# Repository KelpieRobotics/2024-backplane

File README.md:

# 2024-MainBoard
schematics and PCB designs for 2024 MainBoard go here

## how to use

### symbol library
in KiCAD, symbol editor > preferences > manage symbol libraries
press the folder icon and select the file in libs/symbols/

### footprint library
same steps but select the folder in libs/footprints

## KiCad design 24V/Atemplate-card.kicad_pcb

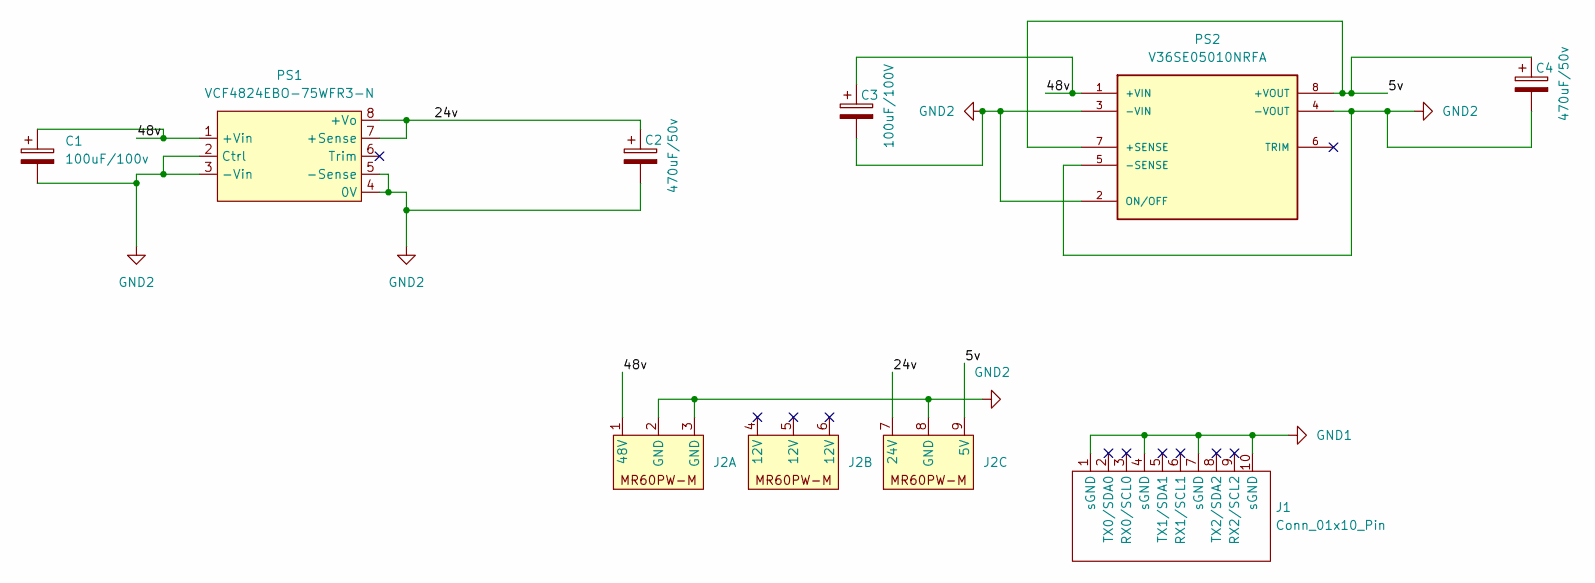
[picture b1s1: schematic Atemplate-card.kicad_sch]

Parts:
C1: 100uF/100v; CP_Elec_10x12.5
C2, C4: 470uF/50v; CP_Elec_10x12.5
C3: 100uF/100V; CP_Elec_10x12.5
J1: Conn_01x10_Pin; CardEdge_2x10
J2: MR60PW-M_X3
PS1: VCF4824EBO-75WFR3-N; Mornsun VCF4824EBO-75WFR3-N
PS2: V36SE05010NRFA; Delta V36SE05010NRFA; PARTREV 03282018

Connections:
/5v: C4.1, J2.9 (5V), PS2.7 (+SENSE), PS2.8 (+VOUT)
/24v: C2.1, J2.7 (24V), PS1.7 (+Sense), PS1.8 (+Vo)
/48v: C1.1, C3.1, J2.1 (48V), PS1.1 (+Vin), PS2.1 (+VIN)
GND1: J1.1 (sGND), J1.4 (sGND), J1.7 (sGND), J1.10 (sGND)
GND2: C1.2, C2.2, C3.2, C4.2, J2.2 (GND), J2.3 (GND), J2.8 (GND), PS1.2 (Ctrl), PS1.3 (-Vin), PS1.4 (0V), PS1.5 (-Sense), PS2.2 (ON/OFF), PS2.3 (-VIN), PS2.4 (-VOUT), PS2.5 (-SENSE)

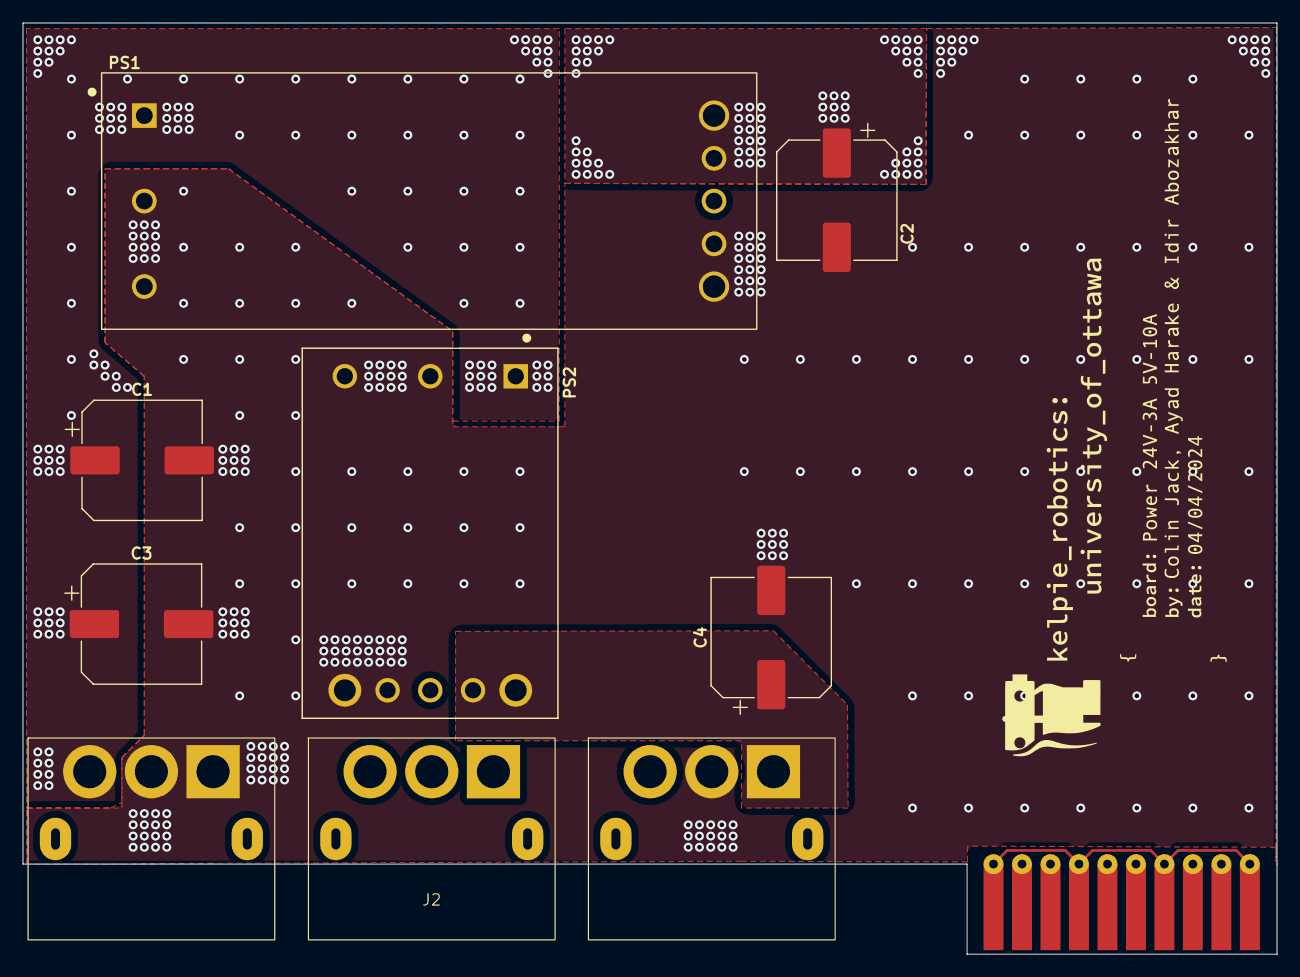
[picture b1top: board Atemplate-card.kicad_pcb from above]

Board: 2 copper layers, 111.8 x 83.0 mm, 8 parts (0 on the bottom side), 5 nets.

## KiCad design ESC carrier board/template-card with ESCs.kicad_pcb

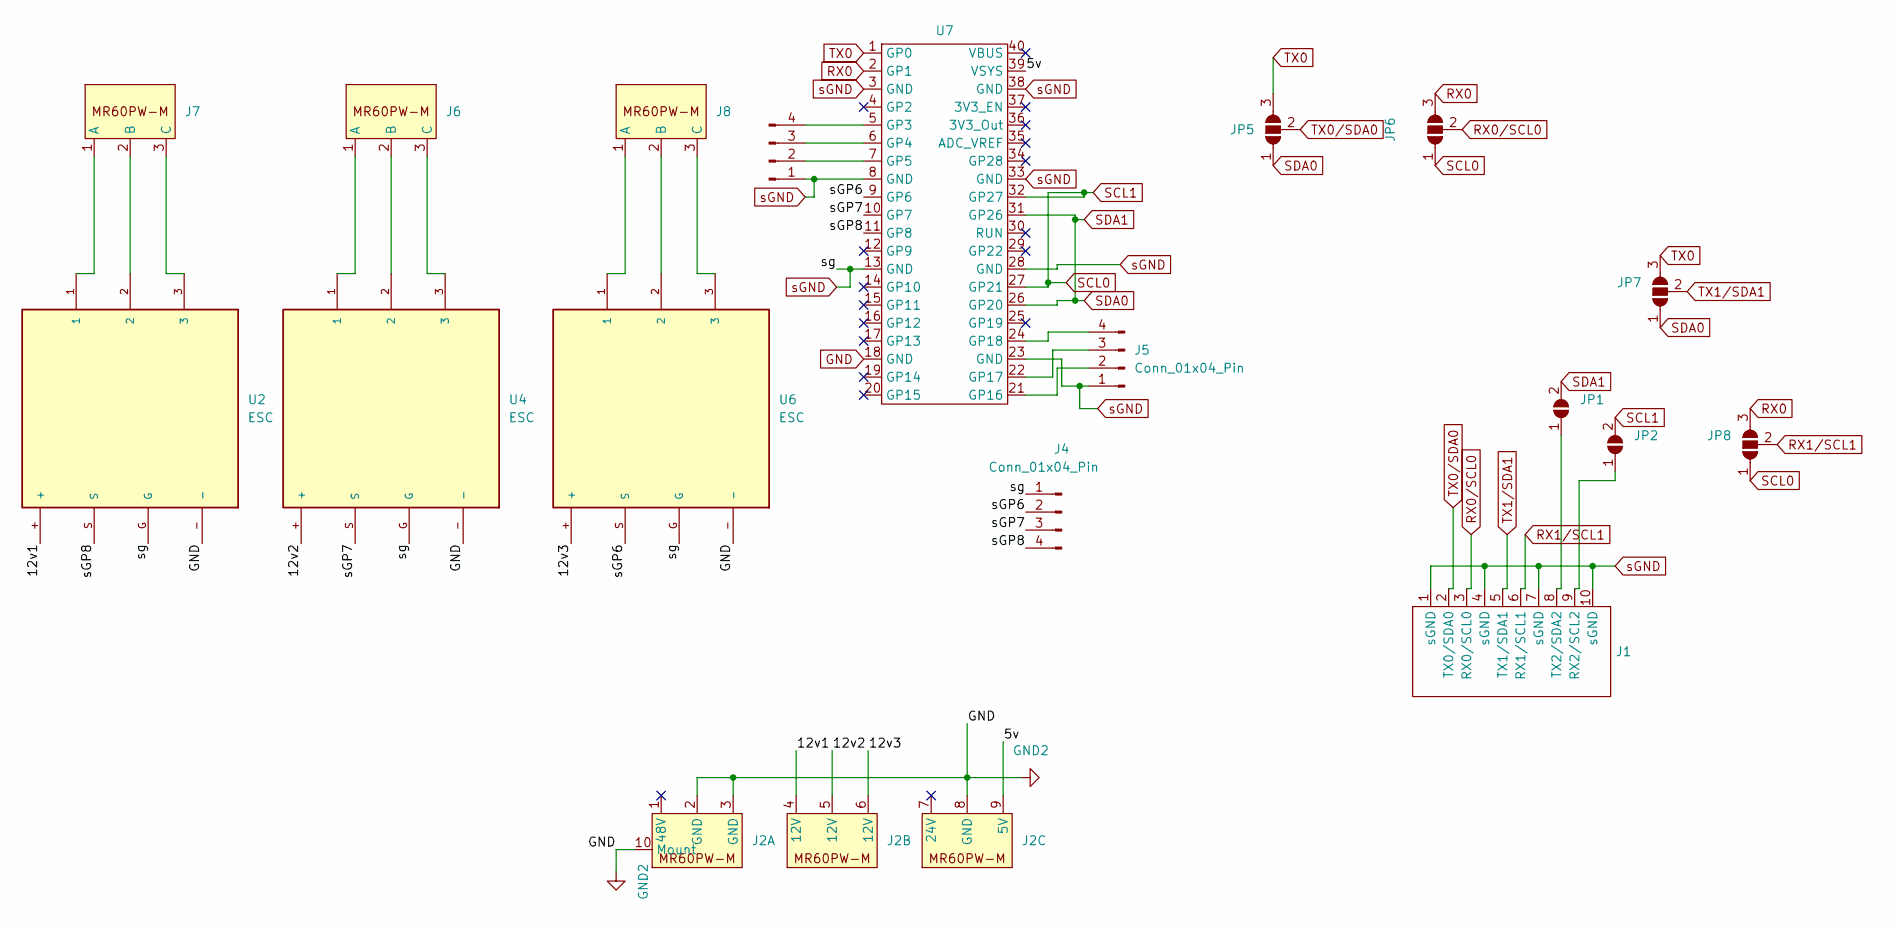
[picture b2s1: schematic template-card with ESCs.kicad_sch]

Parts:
J1: CardEdge_2x10
J2: MR60PW-M_X3
J3, J4, J5: Conn_01x04_Pin; PinHeader_1x04_P2.54mm_Horizontal
J6, J7, J8: MR60PW-M
JP1, JP2: SolderJumper_2_Open; SolderJumper-2_P1.3mm_Open_Pad1.0x1.5mm
JP5, JP6, JP7, JP8: SolderJumper_3_Open; SolderJumper-3_P2.0mm_Open_TrianglePad1.0x1.5mm
U2, U4, U6: ESC
U7: ESP32-S3-Pico

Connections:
/5v: J2.9 (5V), U7.39 (VSYS)
/12v1: J2.4 (12V), U2.+
/12v2: J2.5 (12V), U4.+
/12v3: J2.6 (12V), U6.+
/sGP6: J4.2, U6.S, U7.9 (GP6)
/sGP7: J4.3, U4.S, U7.10 (GP7)
/sGP8: J4.4, U2.S, U7.11 (GP8)
GND: J2.2 (GND), J2.3 (GND), J2.8 (GND), J2.10 (Mount), U2.-, U4.-, U6.-, U7.18 (GND)
unnamed: J1.9 (RX2/SCL2), JP2.1 (A)
unnamed: J1.8 (TX2/SDA2), JP1.1 (A)
unnamed: J3.2, U7.7 (GP5)
unnamed: J3.3, U7.6 (GP4)
unnamed: J3.4, U7.5 (GP3)
unnamed: J5.2, U7.21 (GP16)
unnamed: J5.3, U7.22 (GP17)
unnamed: J5.4, U7.24 (GP18)
unnamed: J6.1 (A), U4.1
unnamed: J6.2 (B), U4.2
unnamed: J6.3 (C), U4.3
unnamed: J7.1 (A), U2.1
unnamed: J7.2 (B), U2.2
unnamed: J7.3 (C), U2.3
unnamed: J8.1 (A), U6.1
unnamed: J8.2 (B), U6.2
unnamed: J8.3 (C), U6.3
RX0: JP6.3 (B), JP8.3 (B), U7.2 (GP1)
RX0/SCL0: J1.3 (RX0/SCL0), JP6.2 (C)
RX1/SCL1: J1.6 (RX1/SCL1), JP8.2 (C)
SCL0: JP2.2 (B), JP6.1 (A), JP8.1 (A), U7.27 (GP21), U7.32 (GP27)
SDA0: JP1.2 (B), JP5.1 (A), JP7.1 (A), U7.26 (GP20), U7.31 (GP26)
TX0: JP5.3 (B), JP7.3 (B), U7.1 (GP0)
TX0/SDA0: J1.2 (TX0/SDA0), JP5.2 (C)
TX1/SDA1: J1.5 (TX1/SDA1), JP7.2 (C)
sGND: J1.1 (sGND), J1.4 (sGND), J1.7 (sGND), J1.10 (sGND), J3.1, J4.1, J5.1, U2.G, U4.G, U6.G, U7.3 (GND), U7.8 (GND), U7.13 (GND), U7.23 (GND), U7.28 (GND), U7.33 (GND), U7.38 (GND)

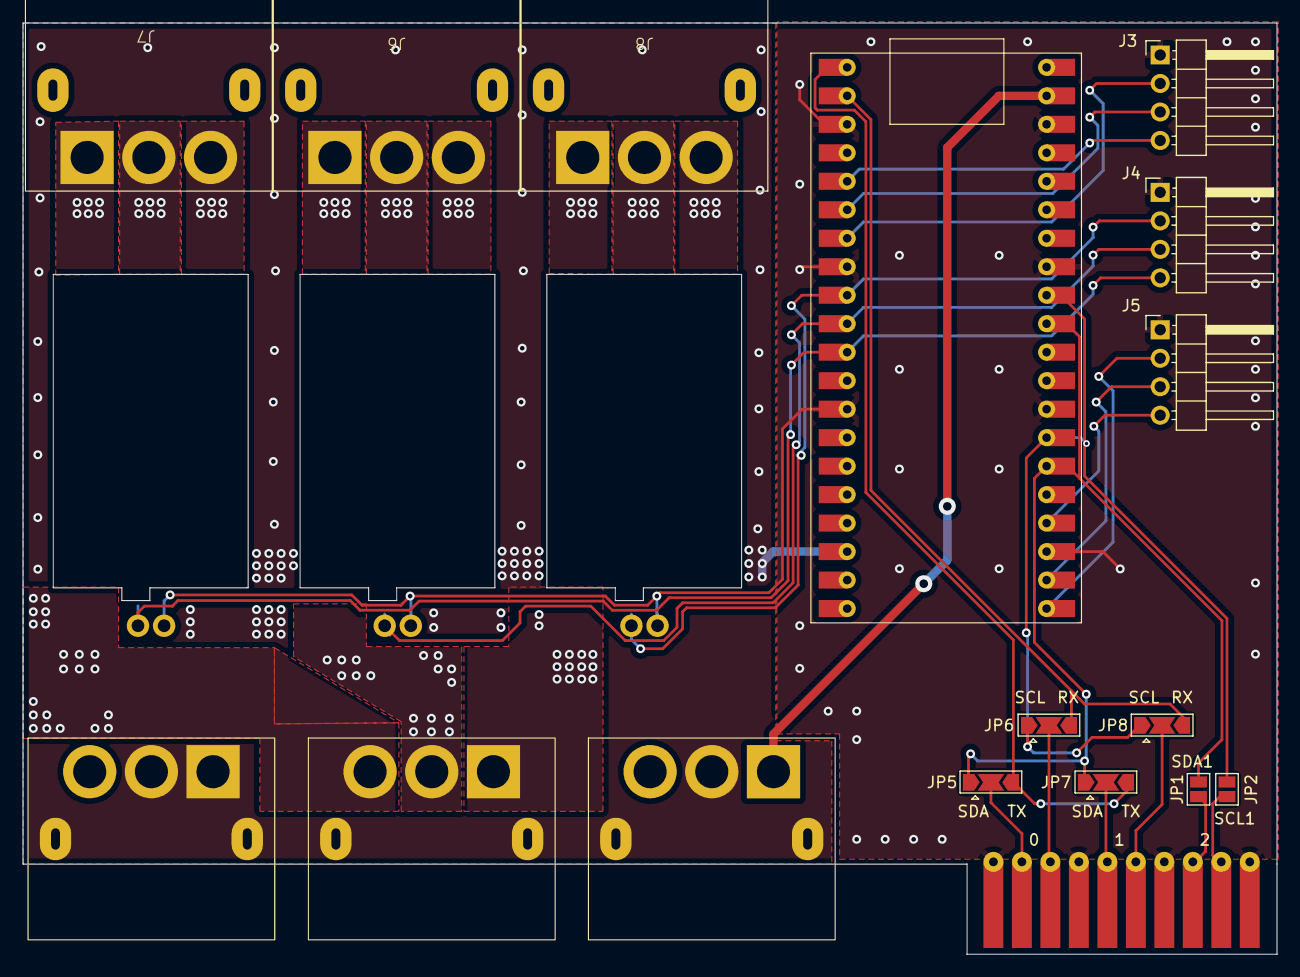
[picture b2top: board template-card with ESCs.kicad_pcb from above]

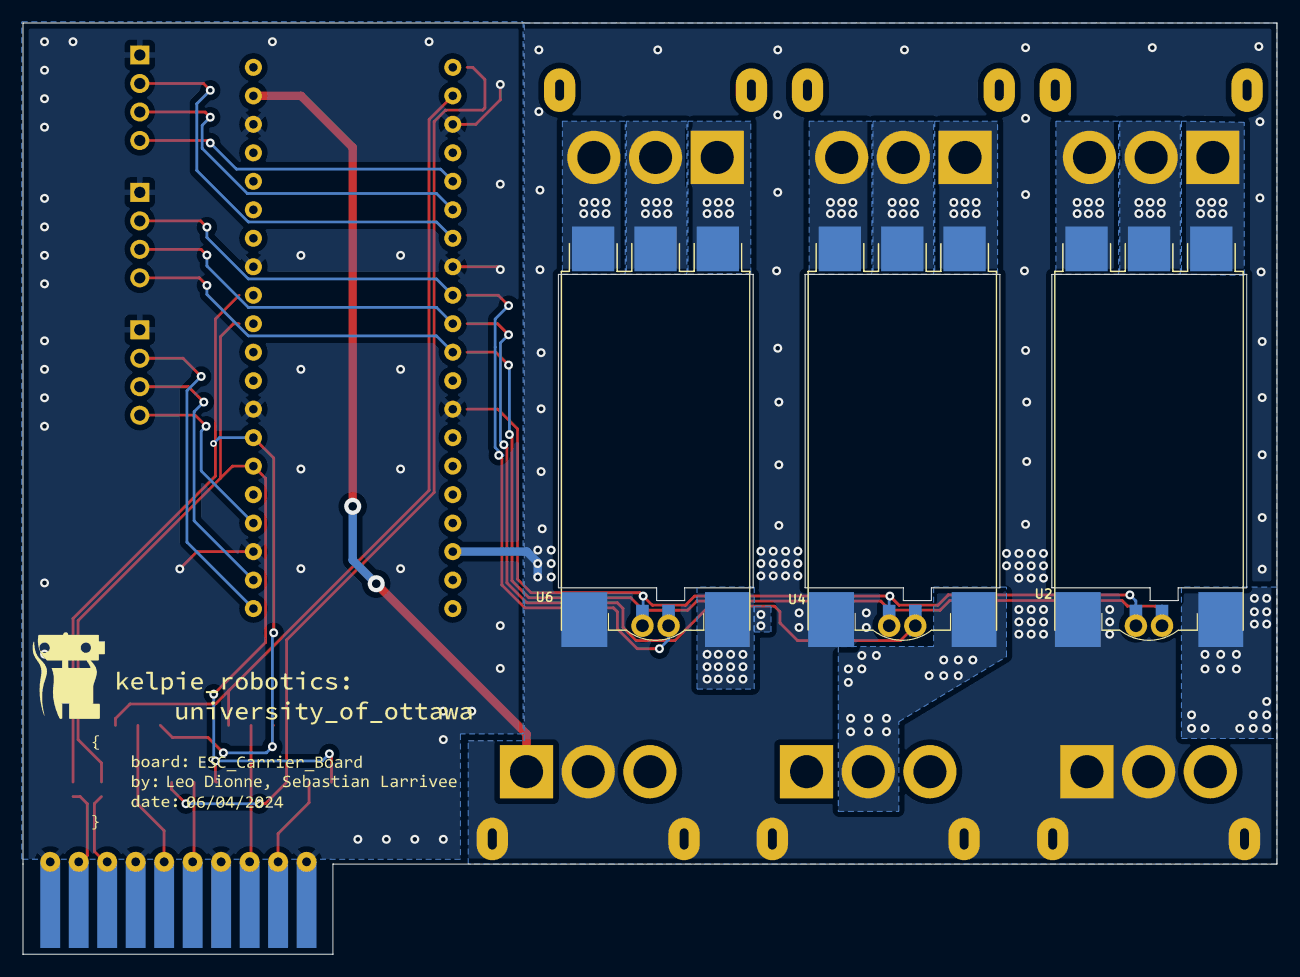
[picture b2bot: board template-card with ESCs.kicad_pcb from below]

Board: 2 copper layers, 111.8 x 83.0 mm, 18 parts (3 on the bottom side), 34 nets.

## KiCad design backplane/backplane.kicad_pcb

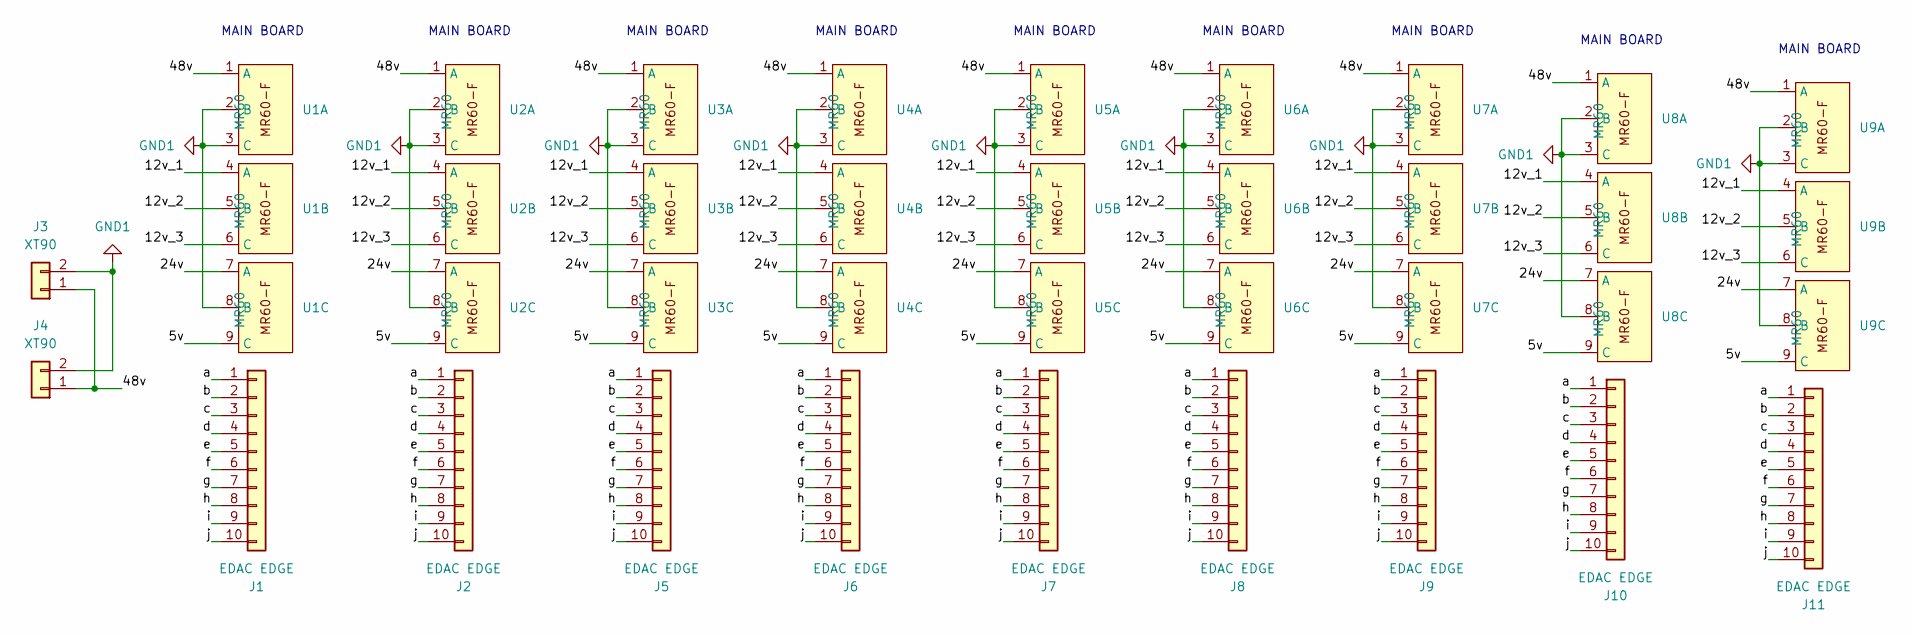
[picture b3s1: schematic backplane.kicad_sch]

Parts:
J1, J2, J5, J6, J7, J8, J9, J10, J11: EDAC EDGE; EDAC_Edge_2x10
J3, J4: XT90; AMASS_XT90PW-M_MOD_NUMS
U1, U2, U3, U4, U5, U6, U7, U8, U9: MR60; MR60-F_X3

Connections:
/5v: U1.9 (C), U2.9 (C), U3.9 (C), U4.9 (C), U5.9 (C), U6.9 (C), U7.9 (C), U8.9 (C), U9.9 (C)
/12v_1: U1.4 (A), U2.4 (A), U3.4 (A), U4.4 (A), U5.4 (A), U6.4 (A), U7.4 (A), U8.4 (A), U9.4 (A)
/12v_2: U1.5 (B), U2.5 (B), U3.5 (B), U4.5 (B), U5.5 (B), U6.5 (B), U7.5 (B), U8.5 (B), U9.5 (B)
/12v_3: U1.6 (C), U2.6 (C), U3.6 (C), U4.6 (C), U5.6 (C), U6.6 (C), U7.6 (C), U8.6 (C), U9.6 (C)
/24v: U1.7 (A), U2.7 (A), U3.7 (A), U4.7 (A), U5.7 (A), U6.7 (A), U7.7 (A), U8.7 (A), U9.7 (A)
/48v: J3.1, J4.1, U1.1 (A), U2.1 (A), U3.1 (A), U4.1 (A), U5.1 (A), U6.1 (A), U7.1 (A), U8.1 (A), U9.1 (A)
/a: J1.1, J2.1, J5.1, J6.1, J7.1, J8.1, J9.1, J10.1, J11.1
/b: J1.2, J2.2, J5.2, J6.2, J7.2, J8.2, J9.2, J10.2, J11.2
/c: J1.3, J2.3, J5.3, J6.3, J7.3, J8.3, J9.3, J10.3, J11.3
/d: J1.4, J2.4, J5.4, J6.4, J7.4, J8.4, J9.4, J10.4, J11.4
/e: J1.5, J2.5, J5.5, J6.5, J7.5, J8.5, J9.5, J10.5, J11.5
/f: J1.6, J2.6, J5.6, J6.6, J7.6, J8.6, J9.6, J10.6, J11.6
/g: J1.7, J2.7, J5.7, J6.7, J7.7, J8.7, J9.7, J10.7, J11.7
/h: J1.8, J2.8, J5.8, J6.8, J7.8, J8.8, J9.8, J10.8, J11.8
/i: J1.9, J2.9, J5.9, J6.9, J7.9, J8.9, J9.9, J10.9, J11.9
/j: J1.10, J2.10, J5.10, J6.10, J7.10, J8.10, J9.10, J10.10, J11.10
GND1: J3.2, J4.2, U1.2 (B), U1.3 (C), U1.8 (B), U2.2 (B), U2.3 (C), U2.8 (B), U3.2 (B), U3.3 (C), U3.8 (B), U4.2 (B), U4.3 (C), U4.8 (B), U5.2 (B), U5.3 (C), U5.8 (B), U6.2 (B), U6.3 (C), U6.8 (B), U7.2 (B), U7.3 (C), U7.8 (B), U8.2 (B), U8.3 (C), U8.8 (B), U9.2 (B), U9.3 (C), U9.8 (B)

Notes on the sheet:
MAIN BOARD

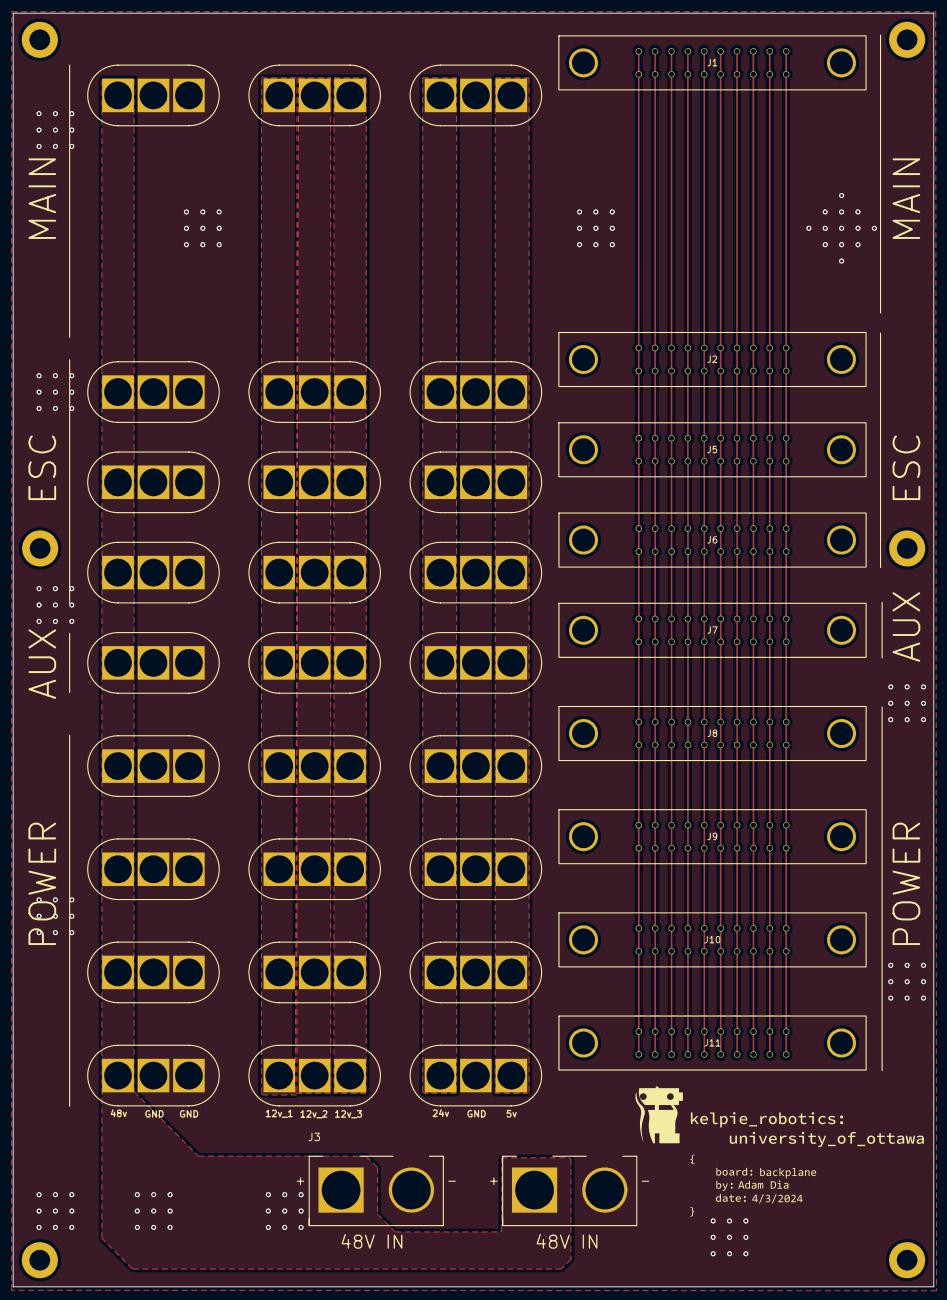
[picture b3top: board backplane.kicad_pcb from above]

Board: 2 copper layers, 142.8 x 197.5 mm, 20 parts (0 on the bottom side), 17 nets.

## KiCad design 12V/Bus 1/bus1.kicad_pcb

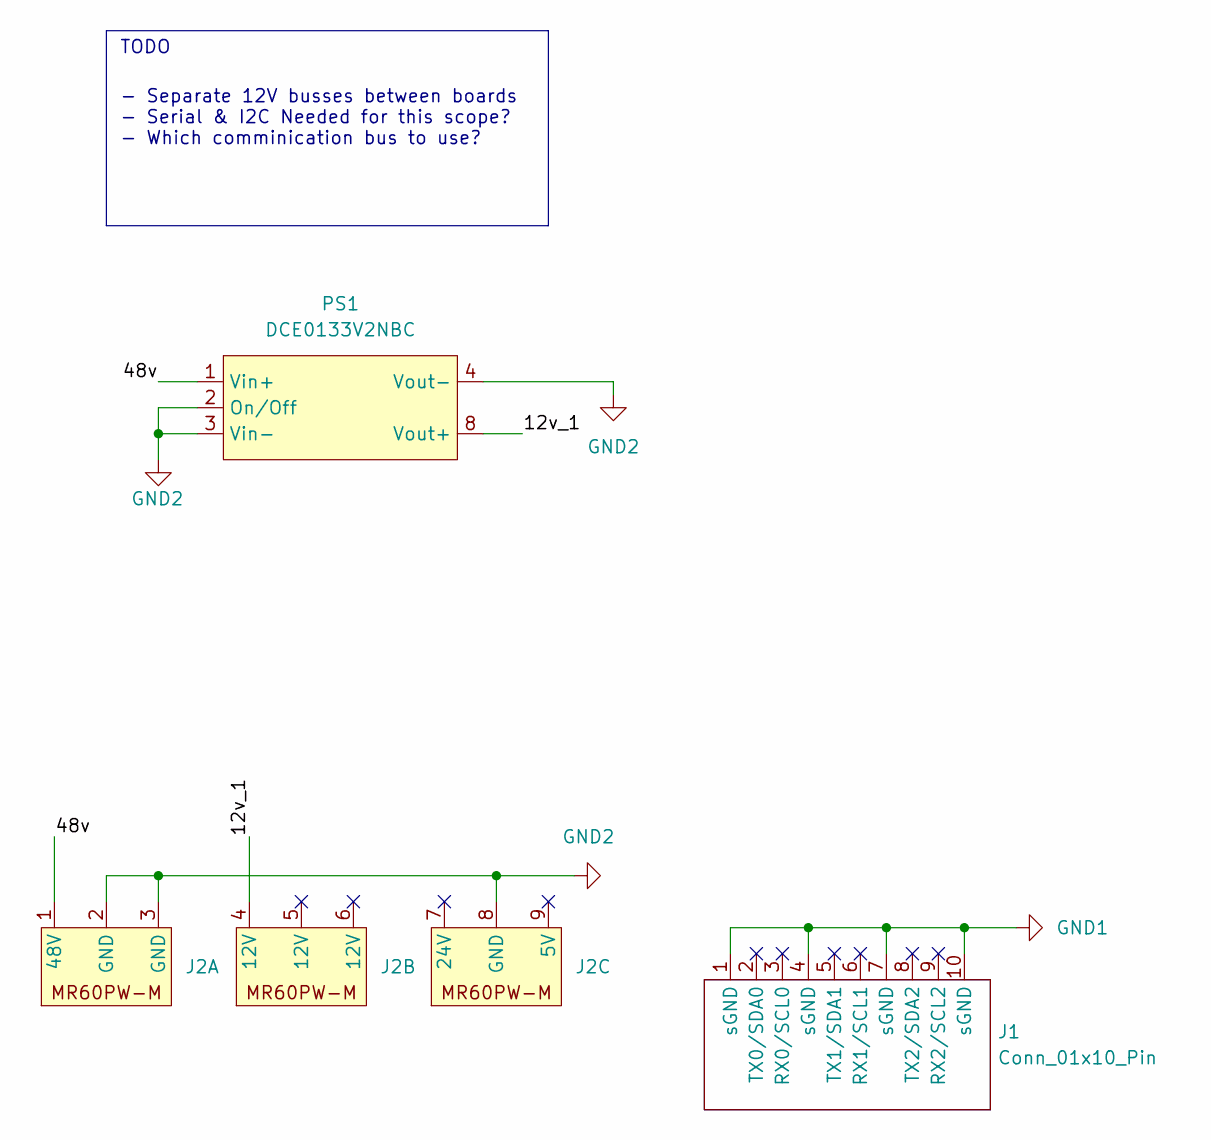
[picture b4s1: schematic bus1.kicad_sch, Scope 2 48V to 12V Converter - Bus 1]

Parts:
J1: Conn_01x10_Pin; CardEdge_2x10
J2: MR60PW-M_X3
PS1: DCE0133V2NBC; Murata DCE0133V2NBC

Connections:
/12v_1: J2.4 (12V), PS1.8 (Vout+)
/48v: J2.1 (48V), PS1.1 (Vin+)
GND1: J1.1 (sGND), J1.4 (sGND), J1.7 (sGND), J1.10 (sGND)
GND2: J2.2 (GND), J2.3 (GND), J2.8 (GND), PS1.2 (On/Off), PS1.3 (Vin-), PS1.4 (Vout-)

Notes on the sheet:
TODO
- Separate 12V busses between boards - Serial & I2C Needed for this scope? - Which comminication bus to use?

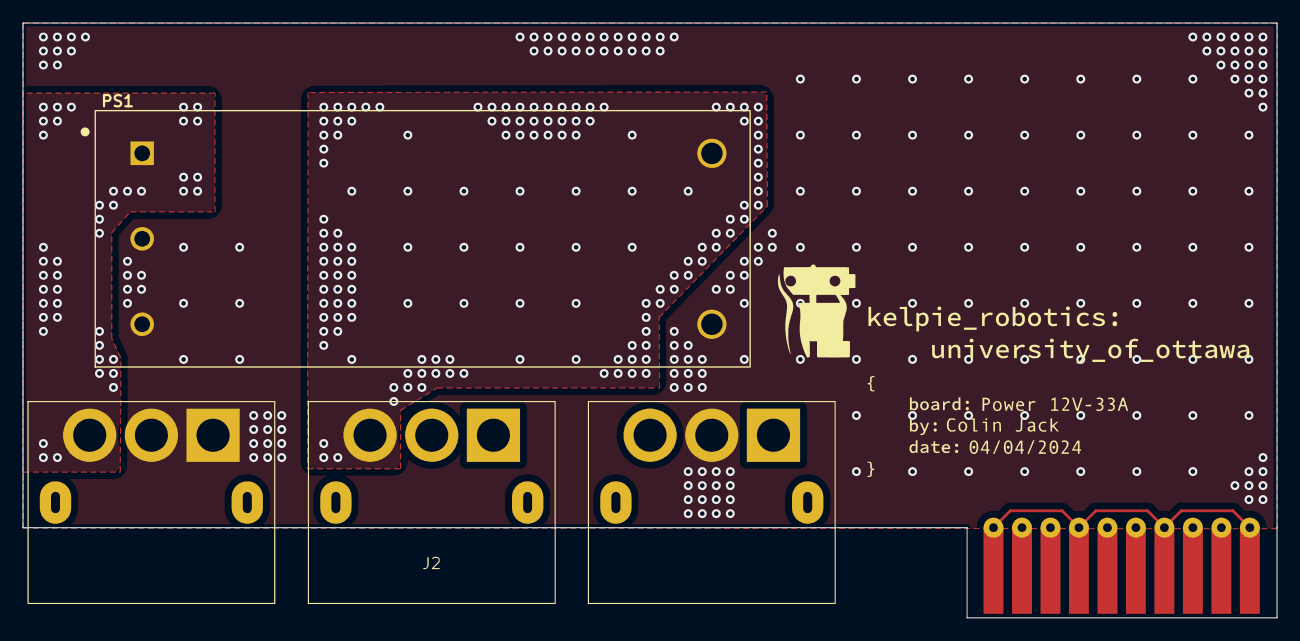
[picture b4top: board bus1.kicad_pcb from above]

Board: 2 copper layers, 111.8 x 53.0 mm, 3 parts (0 on the bottom side), 4 nets.

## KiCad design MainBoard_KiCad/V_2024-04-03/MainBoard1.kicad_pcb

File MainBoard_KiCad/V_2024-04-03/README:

#This directory contains file for the PCB Deisgn before Sebastien Verified them

Side note, sorry I messed up the git ignore

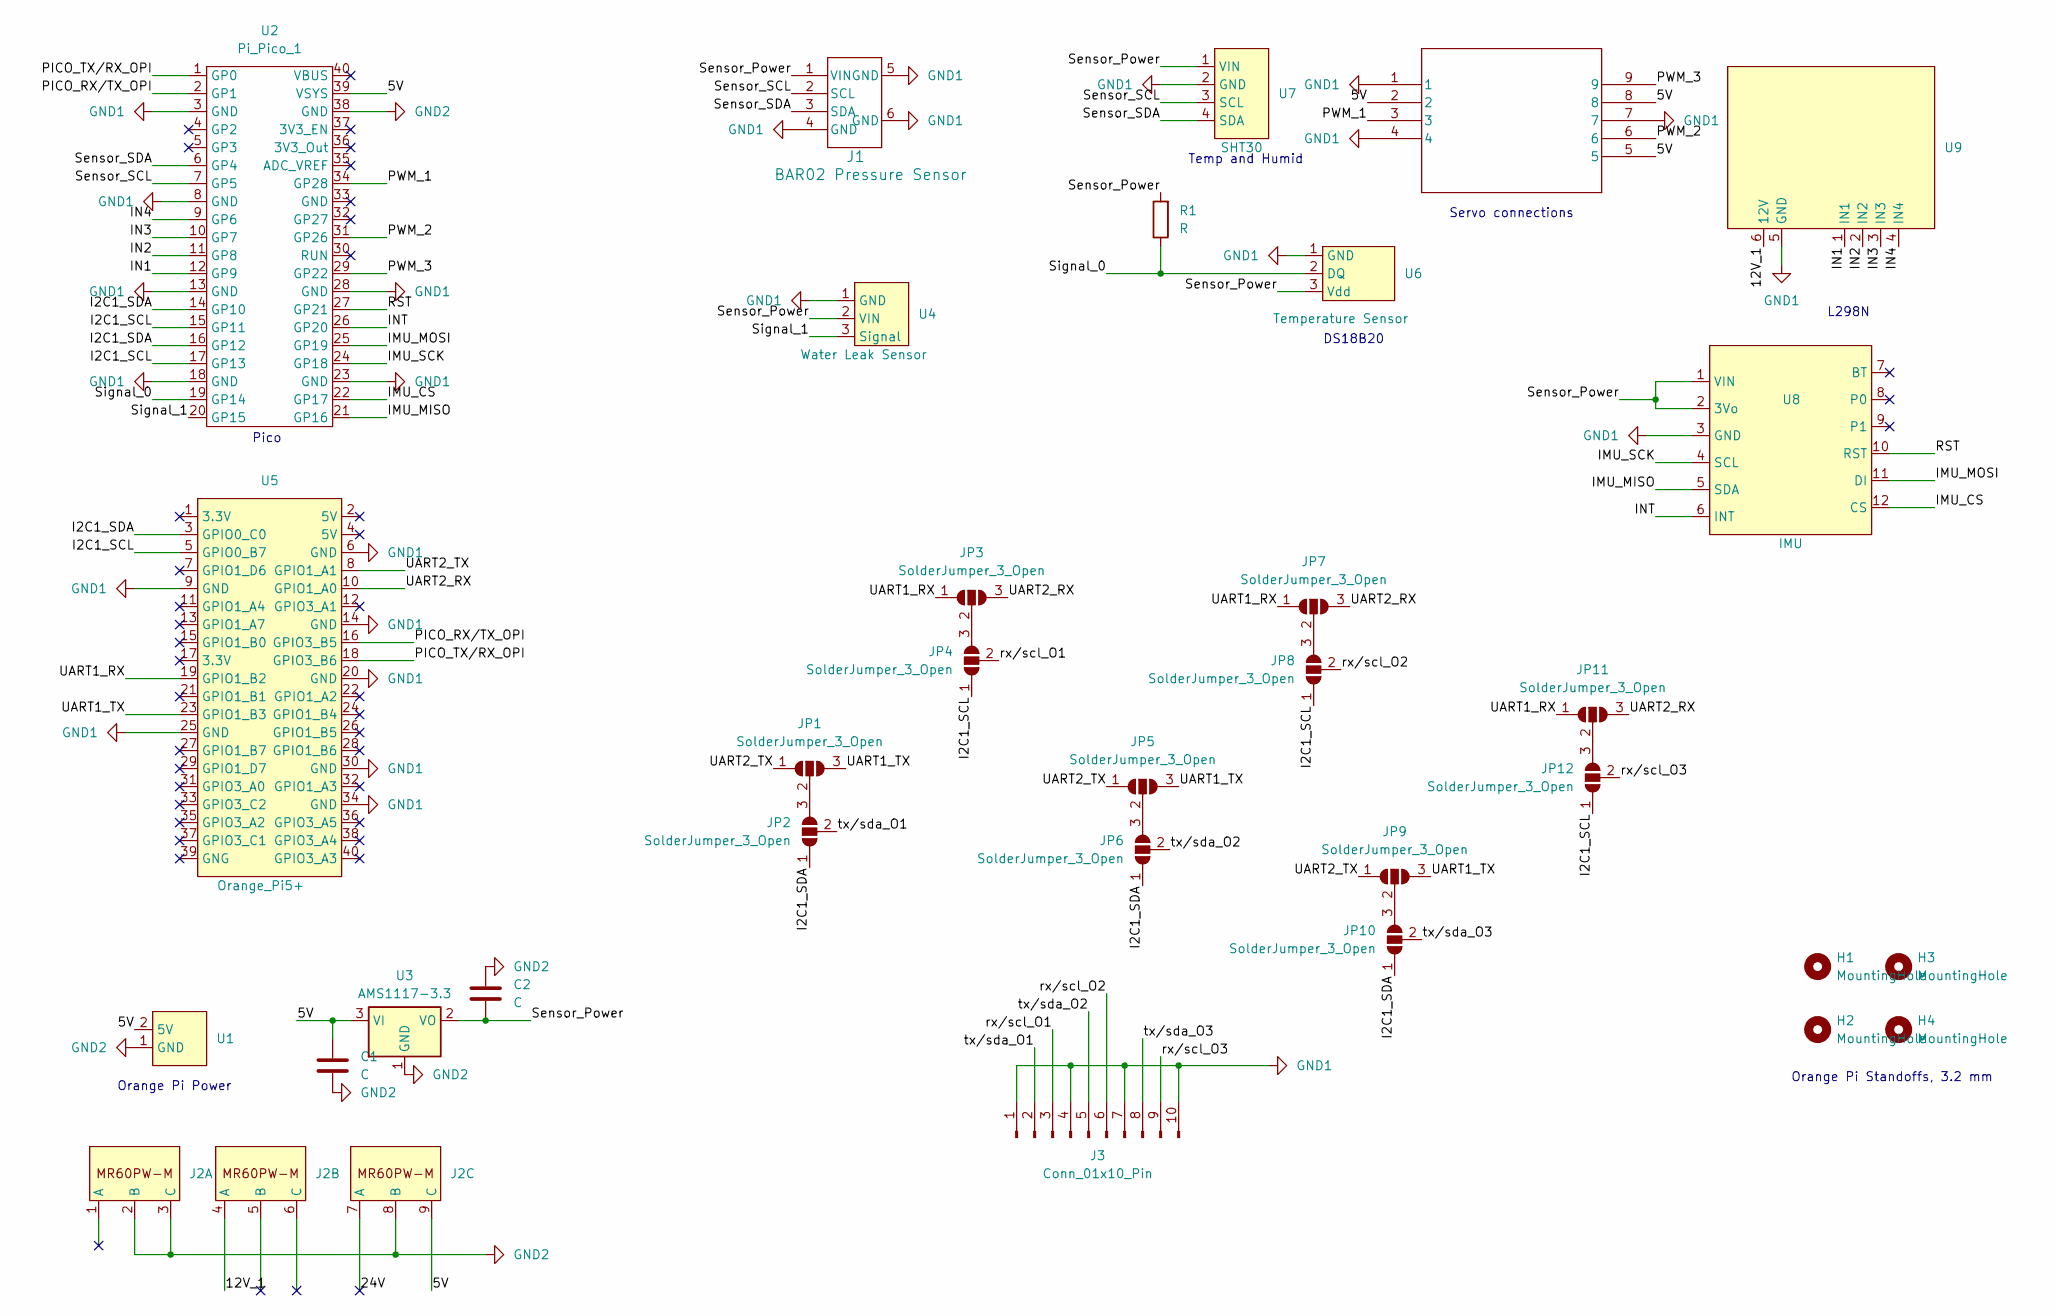
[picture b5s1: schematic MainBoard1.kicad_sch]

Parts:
C1, C2: C; C_0805_2012Metric_Pad1.18x1.45mm_HandSolder
H1, H2, H3, H4: MountingHole; MountingHole_3.2mm_M3
J1: BAR02 Pressure Sensor; JST
J2: MR60PW-M_X3 (2)
J3: Conn_01x10_Pin; CardEdge_2x10 (2)
J4: TSW-103-08-G-T-RA; TSW-103-08-T-T-RA_SAI
JP1, JP2, JP3, JP4, JP5, JP6, JP7, JP8, JP9, JP10, JP11, JP12: SolderJumper_3_Open; SolderJumper-3_P2.0mm_Open_TrianglePad1.0x1.5mm
R1: R; R_0805_2012Metric_Pad1.20x1.40mm_HandSolder
U1: PinHeader_1x02_P2.54mm_Horizontal
U2: Pi_Pico_1; ESP32-S3-Pico
U3: AMS1117-3.3; SOT-223-3_TabPin2
U4: Water Leak Sensor; PinHeader_1x03_P2.54mm_Horizontal
U5: Orange_Pi5+; PinHeader_2x20_P2.54mm_Vertical
U6: Temperature Sensor; PinHeader_1x03_P2.54mm_Horizontal
U7: SHT30
U8: IMU
U9: L298N

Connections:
/5V: C1.2, J2.9 (C), J4.2, J4.5, J4.8, U1.2 (5V), U2.39 (VSYS), U3.3 (VI)
/12V_1: J2.4 (A), U9.6 (12V)
/24V: J2.7 (A)
/I2C1_SCL: JP4.1 (A), JP8.1 (A), JP12.1 (A), U2.15 (GP11), U2.17 (GP13), U5.5 (GPIO0_B7)
/I2C1_SDA: JP2.1 (A), JP6.1 (A), JP10.1 (A), U2.14 (GP10), U2.16 (GP12), U5.3 (GPIO0_C0)
/IMU_CS: U2.22 (GP17), U8.12 (CS)
/IMU_MISO: U2.21 (GP16), U8.5 (SDA)
/IMU_MOSI: U2.25 (GP19), U8.11 (DI)
/IMU_SCK: U2.24 (GP18), U8.4 (SCL)
/IN1: U2.12 (GP9), U9.1 (IN1)
/IN2: U2.11 (GP8), U9.2 (IN2)
/IN3: U2.10 (GP7), U9.3 (IN3)
/IN4: U2.9 (GP6), U9.4 (IN4)
/INT: U2.26 (GP20), U8.6 (INT)
/PICO_RX/TX_OPI: U2.2 (GP1), U5.16 (GPIO3_B5)
/PICO_TX/RX_OPI: U2.1 (GP0), U5.18 (GPIO3_B6)
/PWM_1: J4.3, U2.34 (GP28)
/PWM_2: J4.6, U2.31 (GP26)
/PWM_3: J4.9, U2.29 (GP22)
/RST: U2.27 (GP21), U8.10 (RST)
/Sensor_Power: C2.1, J1.1 (VIN), R1.2, U3.2 (VO), U4.2 (VIN), U6.3 (Vdd), U7.1 (VIN), U8.1 (VIN), U8.2 (3Vo)
/Sensor_SCL: J1.2 (SCL), U2.7 (GP5), U7.3 (SCL)
/Sensor_SDA: J1.3 (SDA), U2.6 (GP4), U7.4 (SDA)
/Signal_0: R1.1, U2.19 (GP14), U6.2 (DQ)
/Signal_1: U2.20 (GP15), U4.3 (Signal)
/UART1_RX: JP3.1 (A), JP7.1 (A), JP11.1 (A), U5.19 (GPIO1_B2)
/UART1_TX: JP1.3 (B), JP5.3 (B), JP9.3 (B), U5.23 (GPIO1_B3)
/UART2_RX: JP3.3 (B), JP7.3 (B), JP11.3 (B), U5.10 (GPIO1_A0)
/UART2_TX: JP1.1 (A), JP5.1 (A), JP9.1 (A), U5.8 (GPIO1_A1)
/rx/scl_O1: J3.3, JP4.2 (C)
/rx/scl_O2: J3.6, JP8.2 (C)
/rx/scl_O3: J3.9, JP12.2 (C)
/tx/sda_O1: J3.2, JP2.2 (C)
/tx/sda_O2: J3.5, JP6.2 (C)
/tx/sda_O3: J3.8, JP10.2 (C)
GND1: J1.4 (GND), J1.5 (GND), J1.6 (GND), J3.1, J3.4, J3.7, J3.10, J4.1, J4.4, J4.7, U2.3 (GND), U2.8 (GND), U2.13 (GND), U2.18 (GND), U2.23 (GND), U2.28 (GND), U4.1 (GND), U5.6 (GND), U5.9 (GND), U5.14 (GND), U5.20 (GND), U5.25 (GND), U5.30 (GND), U5.34 (GND), U6.1 (GND), U7.2 (GND), U8.3 (GND), U9.5 (GND)
GND2: C1.1, C2.2, J2.2 (B), J2.3 (C), J2.8 (B), U1.1 (GND), U2.38 (GND), U3.1 (GND)
unnamed: JP1.2 (C), JP2.3 (B)
unnamed: JP3.2 (C), JP4.3 (B)
unnamed: JP5.2 (C), JP6.3 (B)
unnamed: JP7.2 (C), JP8.3 (B)
unnamed: JP9.2 (C), JP10.3 (B)
unnamed: JP11.2 (C), JP12.3 (B)

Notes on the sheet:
DS18B20
Orange Pi Power
Orange Pi Standoffs, 3.2 mm
Servo connections
Temp and Humid
L298N
Pico

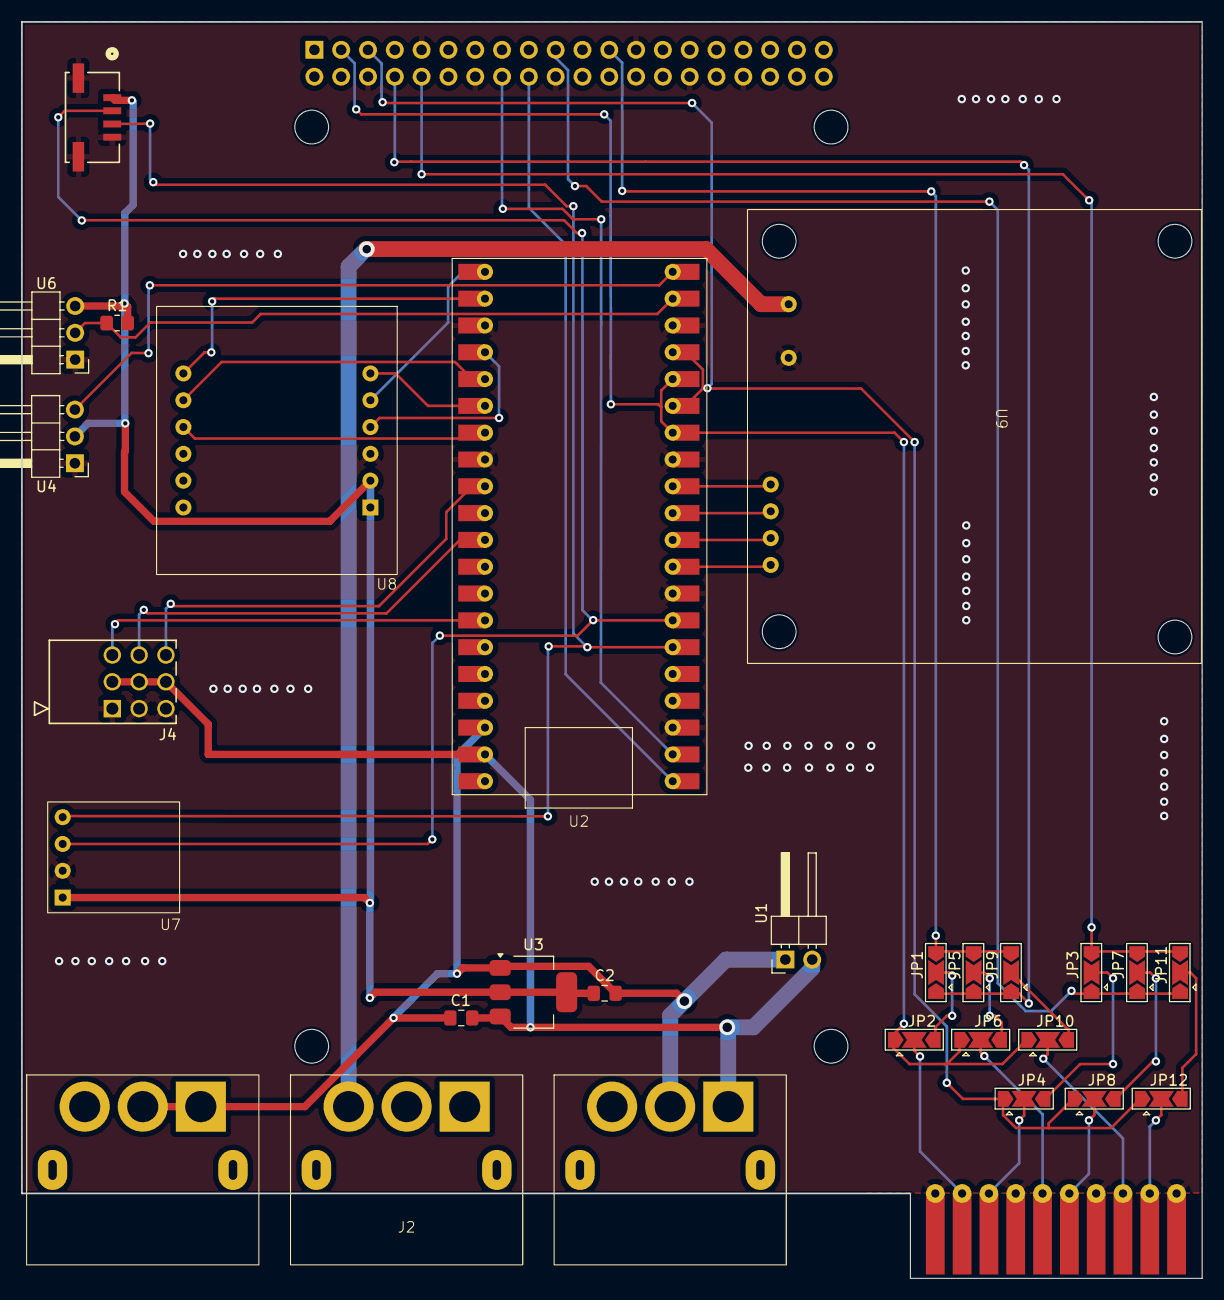
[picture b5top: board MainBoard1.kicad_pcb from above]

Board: 2 copper layers, 111.8 x 119.0 mm, 32 parts (1 on the bottom side), 42 nets.
